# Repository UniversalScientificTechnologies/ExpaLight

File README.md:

[Facebook](https://www.facebook.com/expalight)

# ExpaLight

**ExpaLight** is a red LED flashlight powered by a supercapacitor, designed especially for astronomical observations. The project originated for use during observation nights at summer astronomical schools at the observatory. Thanks to its robust and open-source design, ExpaLight is suitable for both amateur and professional users.

## Technical Parameters

| Parameter           | Value                                |
| ------------------- | ------------------------------------ |
| Stored energy       | 350 J                                |
| Light duration      | \~10 h                               |
| Charging time       | < 50 s (typ.), max. 2 min            |
| Charging indication | Green LED off at 80% voltage         |
| Charging interface  | MicroUSB, ≤500 mA                    |
| Housing             | 3D-printed PLA, durable, water-resistant |
| Light Source        | High-efficiency red LED              |

## Key Features

* **Supercapacitor energy storage** (350 J)
* **Light duration:** up to 10 hours
* **Fast charging:** typically under 50 seconds, max. 2 minutes from full discharge
* **Charging indication:** green LED turns off at \~80% voltage
* **Durable 3D-printed housing**, mechanically and water resistant
* **High-efficiency red LED**, optimized for dark adaptation of the human eye
* **No batteries needed**, USB charging (microUSB)
* **Open-source and repairable**

ExpaLight remains an active project despite repository inactivity. The design was made to withstand years of usage.

[Product manual – Czech version](/DOC/ExpaLight_navod.pdf)

## Why red light?

Astronomers use red light because it preserves the dark adaptation of the human eye, making it ideal for observing the night sky.

## Usage

* Can be placed **horizontally** (ideal for writing into observation logs)
* Can stand **vertically** with LED up or down
* Can be recharged while in use
* Works even when permanently connected to a charger

## Maintenance

* Clean with cloth and mild soapy water
* Do not wash under running water or immerse in liquids
* Avoid abrasive tools to prevent scratching the housing

## Frequently Asked Questions

**Do I need to switch it off?**
No. The flashlight has no mechanical switch. It shines until fully discharged, then you recharge it via USB.

**Why this shape?**
The hexagonal body prevents rolling, ensures stable positioning on surfaces, and supports versatile use (e.g. headlamp attachment in future).

**Can I leave it charging permanently?**
Yes. The electronics are designed to handle permanent connection safely.

**What happens if it is fully discharged?**
Nothing. Unlike battery-based lamps, the supercapacitor can be fully discharged without degradation.

**Can I use a mobile charger?**
Yes. Any standard microUSB charger (5V, ≤500 mA) or USB port will work. Some smart chargers may fail due to low current draw — in that case, use another charger.

## Availability

You can purchase ExpaLight at [Tindie](https://www.tindie.com/products/10265/) or contact us directly at **[sale@ust.cz](mailto:sale@ust.cz)**.

## Contributions

ExpaLight is an open-source hardware project. Suggestions and improvements are welcome! Please open an issue in the [GitHub tracker](https://github.com/UniversalScientificTechnologies/ExpaLight/issues).

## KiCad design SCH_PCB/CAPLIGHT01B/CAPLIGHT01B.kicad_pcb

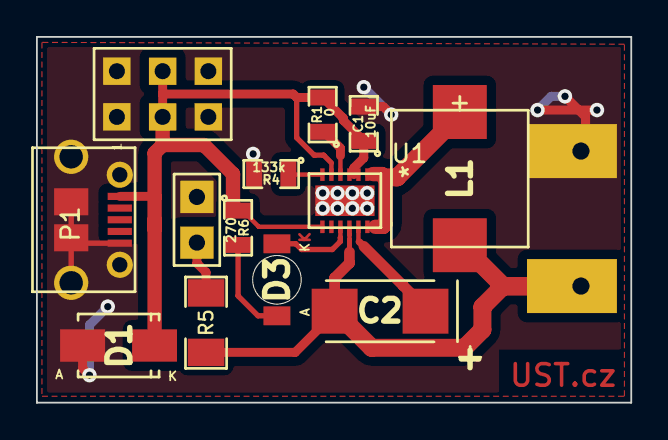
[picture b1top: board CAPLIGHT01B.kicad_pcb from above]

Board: 2 copper layers, 33.0 x 20.3 mm, 14 parts (1 on the bottom side), 10 nets.

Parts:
C1: 10uF; SMD-0805
C2: 100uF; TantalC_SizeC_Reflow
C3: 50F; C_Radial_D18_L25_P7.5_BAT
D1: M4; SMA_Standard
D2: LED; Straight_1x02
D3: LED; LED_1206
J1: JUMP_3X2; Straight_2x03
L1: DER0705-3.3uH; DER0705
P1: USB_OTG; uUSB-B
R1: 0; SMD-0805
R4: 133k; SMD-0805
R5: 68; SMD-1206
R6: 270; SMD-0805
U1: LTC3625; DFN-12-1EP_3x4mm_Pitch0.5mm

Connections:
/PG: D3.1, U1.9
/VIN: C1.1, D1.2, J1.3, J1.4, P1.1, R1.2, R6.1, U1.2, U1.3, U1.5, U1.7
GND: C1.2, C3.2, D1.1, D2.1, J1.1, J1.2, J1.5, J1.6, P1.5, R4.2, U1.13
unnamed: C2.1, U1.11
unnamed: C2.2, C3.1, L1.2, R5.1, U1.10
unnamed: D2.2, R5.2
unnamed: D3.2, R6.2
unnamed: L1.1, U1.1, U1.12
unnamed: R1.1, U1.4
unnamed: R4.1, U1.6

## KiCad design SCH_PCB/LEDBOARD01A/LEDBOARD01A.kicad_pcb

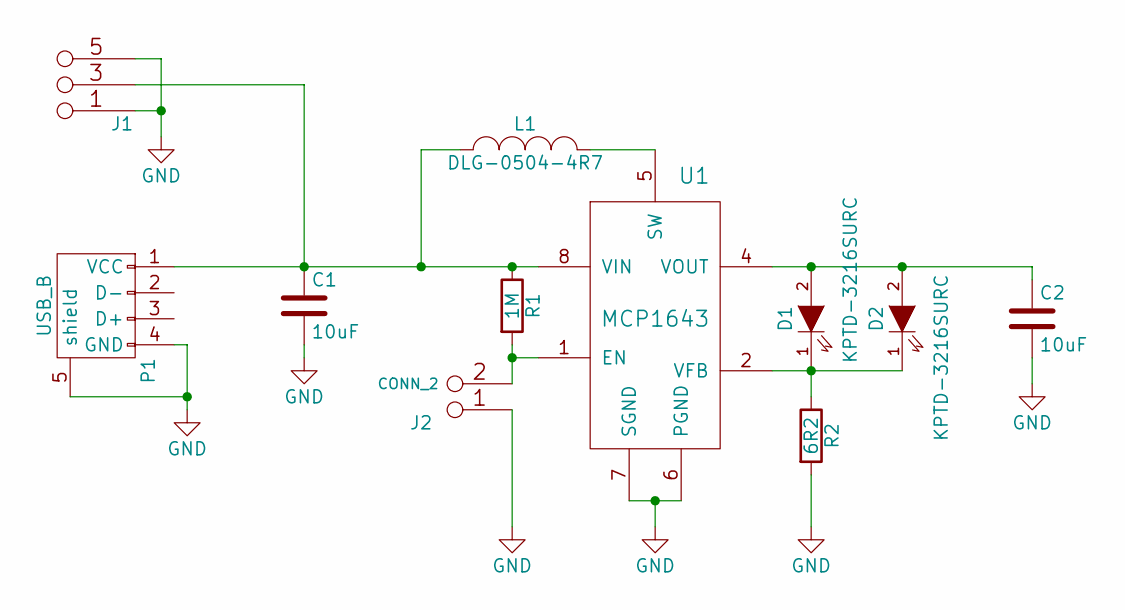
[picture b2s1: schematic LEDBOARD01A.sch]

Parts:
C1, C2: 10uF; SMD-0805
D1, D2: KPTD-3216SURC; LED_1206
J1: JUMP_3X2; Straight_2x03
J2: CONN_2; Straight_1x02
L1: DLG-0504-4R7; DLG0504
P1: USB_B; uUSB-B
R1: 1M; SMD-0805
R2: 6R2; SMD-0805
U1: MCP1643; MSOP-8_3x3mm_Pitch0.65mm

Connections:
GND: C1.2, C2.2, J1.1 (2), J1.2, J1.5 (6), J1.6, J2.1, P1.4 (GND), P1.5 (shield), R2.2, U1.6 (PGND), U1.7 (SGND)
unnamed: C1.1, J1.3 (4), J1.4, L1.1, P1.1 (VCC), R1.1, U1.8 (VIN)
unnamed: C2.1, D1.2 (A), D2.2 (A), U1.4 (VOUT)
unnamed: D1.1 (K), D2.1 (K), R2.1, U1.2 (VFB)
unnamed: J2.2 (PM), R1.2, U1.1 (EN)
unnamed: L1.2, U1.5 (SW)

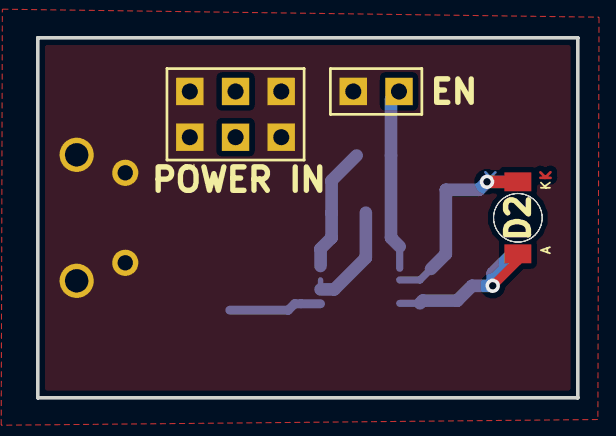
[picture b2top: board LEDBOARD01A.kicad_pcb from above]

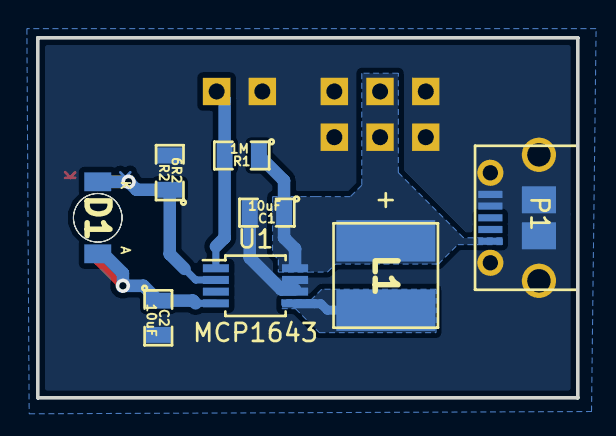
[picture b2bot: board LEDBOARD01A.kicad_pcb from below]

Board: 2 copper layers, 30.0 x 20.0 mm, 11 parts (8 on the bottom side), 6 nets.

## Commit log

2016-03-08 Init - Existing model
2016-03-08 Dual capacitor version -- old is in another branch
2016-03-08 Revert "Dual capacitor version -- old is in another branch"
    This reverts commit 619fe175ac76aeb91642d036e20cf4a3dc257476.
2016-03-09 describe
2016-03-09 light body
2016-03-09 add case
2016-03-09 renderovani pro expu
2016-03-09 readme
2016-03-10 parabolic led view, PCB spacers, PCB space
2016-03-10 New Thread_lib
2016-03-11 edits
2016-03-12 Readme updated and todo ideas moved to separate file.
2016-03-21 Creation PCB
2016-04-20 Modifications
2016-04-27 move .scad files to /CAD/
2016-04-27 render
2016-06-07 Project bug tracking update.
2016-06-26 Add Gitter badge
2016-06-28 SuperCap module with led
2016-06-28 clean
2016-07-01 nová verze
2016-07-02 Second capacitor SMD pad
2016-07-02 pcb labels
2016-07-02 label
2016-07-03 only for ExpaLight
2016-07-03 layout edit
2016-07-03 Datasheets included.
2016-07-03 tracks width
2016-07-03 clear folder
2016-07-03 pdf update
2016-07-06 New charge indicating LED added. Manufacturing files generated.
2016-07-06 Capacitor graphics removed.
2016-07-06 Silkscreen updated.
2016-07-21 case edist
2016-07-21 printable parts
2016-07-21 script for rendering
2016-08-06 printed case update
2016-08-06 Design bugs notes.
2016-08-09 add photo
2016-08-09 small image
2016-08-10 Components values in schema changed to real values populated on PCBs. A photo added to the readme file.
2016-08-15 Uprava README podle Lenky ...
2016-08-17 New flashlight photos.
2016-08-19 Improved PCB layout for easier manufacturing.
2016-10-08 edit model size
2016-10-10 add hole to cap
2016-10-14 Opravy výrobní data
    Generována nová data. Zvětšen otvor pro C 50F.
2016-10-17 cap with spring
2016-10-21 Supplementing identification devices
2016-10-27 NEW PHOTOS
2016-10-28 add new files
2016-10-29 add gcode
2016-10-29 ini files
2016-10-29 git add .
2016-11-25 new render
2016-11-30 clean repository
2016-12-06 add spring
2016-12-06 spring edit, squarly end
2016-12-06 source file update
2016-12-06 spring - remove sharp edge
2016-12-07 shorter spring
2016-12-10 Possible improvement noted.
2016-12-10 better edges, bigger hole for led.
2016-12-10 TODO updated. ;
2016-12-12 dira u led d=3mm, posun PCB smerem od LED, vetsi misto na C
2016-12-12 new spacing
2017-02-14 navod pro expalight
2017-02-14 navod expalight
2017-03-06 new manual
2017-08-10 Documentation updated, english texts improved. Idicator LED changed to green in schematics.
2017-08-10 PDF plot of schematics updated.
2017-12-07 Photo documentation updated.
2017-12-07 Open-source statement added.
2017-12-09 pridani popisu ze zruseneho obchodu na facebooku.
2017-12-14 User manual updated.
2021-11-18 Update renders.
2025-08-19 Update readme.
2025-08-19 Save existing tindie listing before change.
2025-08-19 Updated Tindie listing.
